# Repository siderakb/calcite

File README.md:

# Calcite

Kailh Choc V1 (aka PG1350) low profile switches ortho keyboard, includes PCB and CNC/3DP case, inspired by [ARTSEY](https://artsey.io/), [Home row mods](https://precondition.github.io/home-row-mods) and Preonic/Planck keyboard. 

> The keycap in the above picture is from Keychron K1 v2.

## Note

Gerber, BOM and CPL files are generated by [KiCad JLCPCB Tools](https://github.com/Bouni/kicad-jlcpcb-tools) plugin.  

I use [KiCAD KLE Placer](https://github.com/zykrah/kicad-kle-placer) plugin to automatically place switch footprints.

If `key-switches.pretty` folder is empty, use `git submodule update --init` to clone submodule.

## Disclaimer

These files are provided without warranty of any kind.  
It is recommended to check yourself before manufacturing and use.

For the full statement, plase see [LICENSE](./LICENSE).

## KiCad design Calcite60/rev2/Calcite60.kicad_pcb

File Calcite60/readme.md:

# Calcite60

A 60 keys ortho Kailh Choc V1 keyboard.

- Preonic V3 compatible (Mounting holes, USB and RESET button).
- Kailh Choc V1 low profile switches (PG1350), optional 2U keys.
- USB Type-C with ESD protection and resettable fuse.
- RP2040 ARM MCU, 16MB external flash.
- One configurable monochrome LED indicator.
- Powered by [QMK](https://github.com/qmk/qmk_firmware) firmware.
- Support [Vial](https://get.vial.today), edit keymap and configure keyboard in real time.
- JLCPCB's PCBA service available.

## PCB

Online preview available [here](https://kicanvas.org/?github=https%3A%2F%2Fgithub.com%2Fsiderakb%2Fcalcite%2Ftree%2Fmain%2FCalcite60%2Fpcb), powered by [KiCanvas](https://kicanvas.org/)

|        |               Preview                |
| ------ | :----------------------------------: |
| Front  |  |
| Back   |  |
| Layers |  |

### Board Characteristics

- Copper layer count: 2
- Board thickness: 1.6 mm
- Board overall dimensions: 226 mm x 94.15 mm
- Min track/spacing: 0.13 mm / 0.13 mm
- Min hole diameter: 0.3 mm
- Castellated pads: No
- Edge card connectors: No
- Plated board edge: No

## Screw

- 4* M2x2~4, 90° flat head

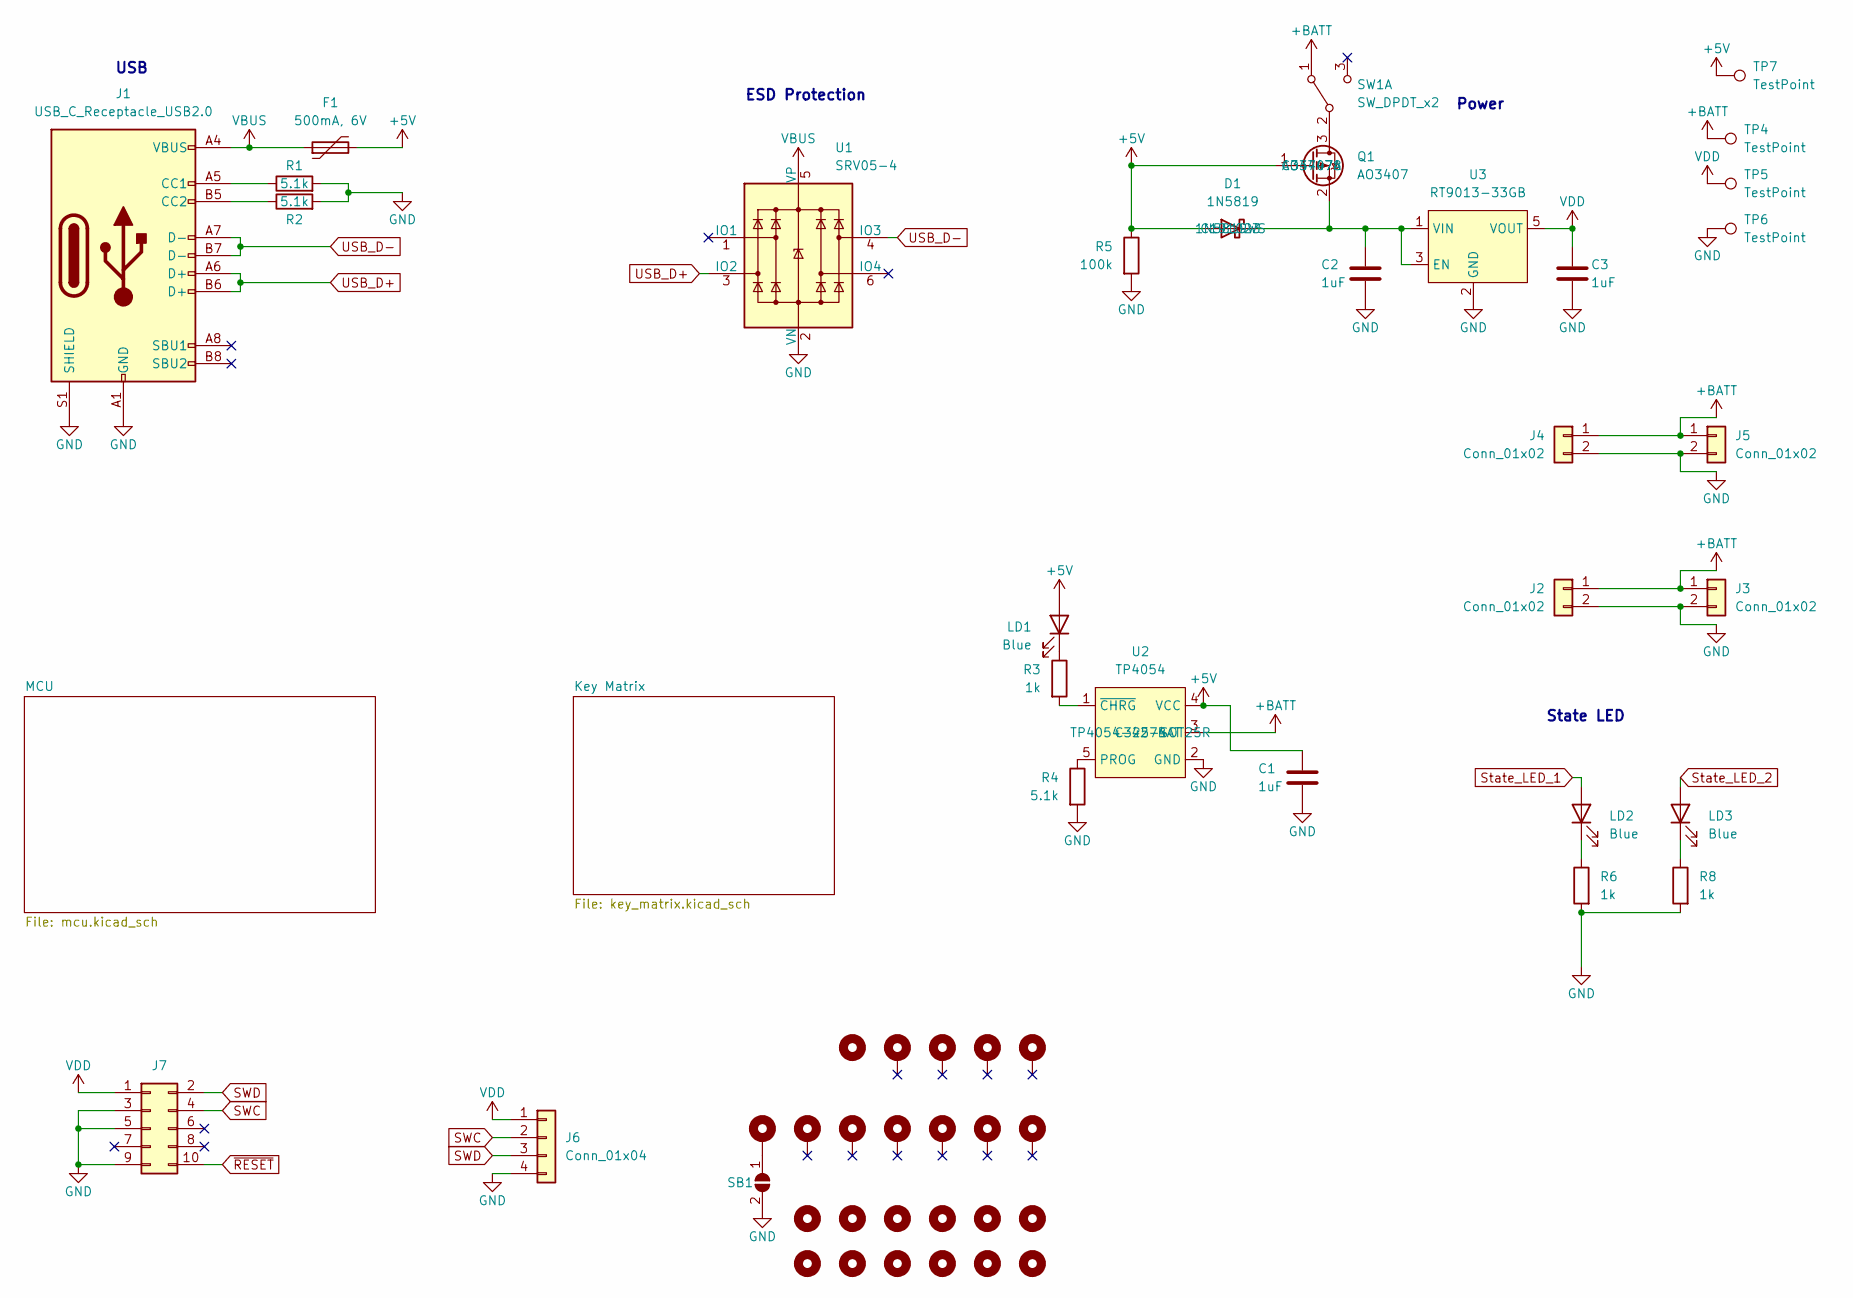
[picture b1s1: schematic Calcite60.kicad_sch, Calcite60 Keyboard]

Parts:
C1, C2, C3: 1uF; C_0603_1608Metric; MFR. Part # CL10A105KB8NNNC; LCSC C15849
D1: 1N5819; D_SOD-323_HandSoldering; MFR. Part # 1N5819WS; LCSC C191023
F1: 500mA, 6V; Fuse_0805_2012Metric; MFR. Part # SMD0805B050TF; LCSC C269104
H1, H2, H4, H6, H8, H10, H12, H14, H15, H16, H17: MountingHole; MountingWuerth_M2; MFR. Part # 9774025243R; LCSC C9900035855
H5, H18, H19, H20, H21, H22, H23, H24, H25: MountingHole; mouse_bite
H7, H9, H11, H13: MountingHole; MountingHale_M2
J1: USB_C_Receptacle_USB2.0; USB_C_Receptacle_HRO_TYPE-C-31-M-12; MFR. Part # TYPE-C-31-M-12; LCSC C165948
J2, J4: Conn_01x02; PinHeader_1x02_P2.54mm_Vertical
J3, J5: Conn_01x02; JST_PH_S2B-PH-K_1x02_P2.00mm_Horizontal
J6: Conn_01x04; PinHeader_1x04_P2.54mm_Vertical
J7: Conn_02x05_Counter_Clockwise; 10pin SWD
LD1, LD2, LD3: Blue; LED_0603_1608Metric; MFR. Part # 19-217/GHC-YR1S2/3T; LCSC C72043
Q1: AO3407; SOT-23; MFR. Part # AO3407A; LCSC C347478
R1, R2, R4: 5.1k; R_0603_1608Metric; MFR. Part # 0603WAF5101T5E; LCSC C23186
R3, R6, R8: 1k; R_0603_1608Metric; MFR. Part # 0603WAF1001T5E; LCSC C21190
R5: 100k; R_0603_1608Metric; MFR. Part # 0603WAF1003T5E; LCSC C25803
SB1: SolderJumper_2_Open; SolderJumper-2_P1.3mm_Open_TrianglePad1.0x1.5mm
SW1: SW_DPDT_x2; 9_3.5_3.5 Switch
TP4, TP5, TP6, TP7: TestPoint; TestPoint_Pad_D1.5mm
U1: SRV05-4; SOT-23-6; MFR. Part # SRV05-4-P-T7; LCSC C85364
U2: TP4054; SOT-23-5; MFR. Part # TP4054-42-SOT25R; LCSC C32574
U3: RT9013-33GB; SOT-23-5; MFR. Part # TPRT9013-33GB; LCSC C587158

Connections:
+5V: C1.1, D1.2 (A), F1.2, LD1.2 (A), Q1.1 (G), R5.1, TP7.1, U2.4 (VCC); also elsewhere on the board
+BATT: J2.1, J3.1, J4.1, J5.1, SW1.1 (A), TP4.1, U2.3 (BAT); also elsewhere on the board
GND: C1.2, C2.2, C3.2, J1.A1 (GND), J1.A12 (GND), J1.B1 (GND), J1.B12 (GND), J1.S1 (SHIELD), J2.2, J3.2, J4.2, J5.2, J6.4, J7.3, J7.5, J7.9, R1.2, R2.2, R4.2, R5.2, R6.2, R8.2, SB1.2 (B), TP6.1, U1.2 (VN), U2.2 (GND), U3.2 (GND); also elsewhere on the board
unnamed: C2.1, D1.1 (K), Q1.2 (S), U3.1 (VIN), U3.3 (EN)
unnamed: J1.A5 (CC1), R1.1
unnamed: J1.B5 (CC2), R2.1
unnamed: LD1.1 (K), R3.1
unnamed: LD2.1 (K), R6.1
unnamed: LD3.1 (K), R8.1
unnamed: Q1.3 (D), SW1.2 (B)
unnamed: H1.1, SB1.1 (A)
unnamed: R4.1, U2.5 (PROG)
unnamed: R3.2, U2.1 (~CHRG)
SWC: J6.2, J7.4; also elsewhere on the board
SWD: J6.3, J7.2; also elsewhere on the board
State_LED_1: LD2.2 (A); also elsewhere on the board
State_LED_2: LD3.2 (A); also elsewhere on the board
USB_D+: J1.A6 (D+), J1.B6 (D+), U1.3 (IO2); also elsewhere on the board
USB_D-: J1.A7 (D-), J1.B7 (D-), U1.4 (IO3); also elsewhere on the board
VBUS: F1.1, J1.A4 (VBUS), J1.A9 (VBUS), J1.B4 (VBUS), J1.B9 (VBUS), U1.5 (VP)
VDD: C3.1, J6.1, J7.1, TP5.1, U3.5 (VOUT); also elsewhere on the board
~RESET: J7.10; also elsewhere on the board

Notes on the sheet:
ESD Protection
State LED
USB
Power

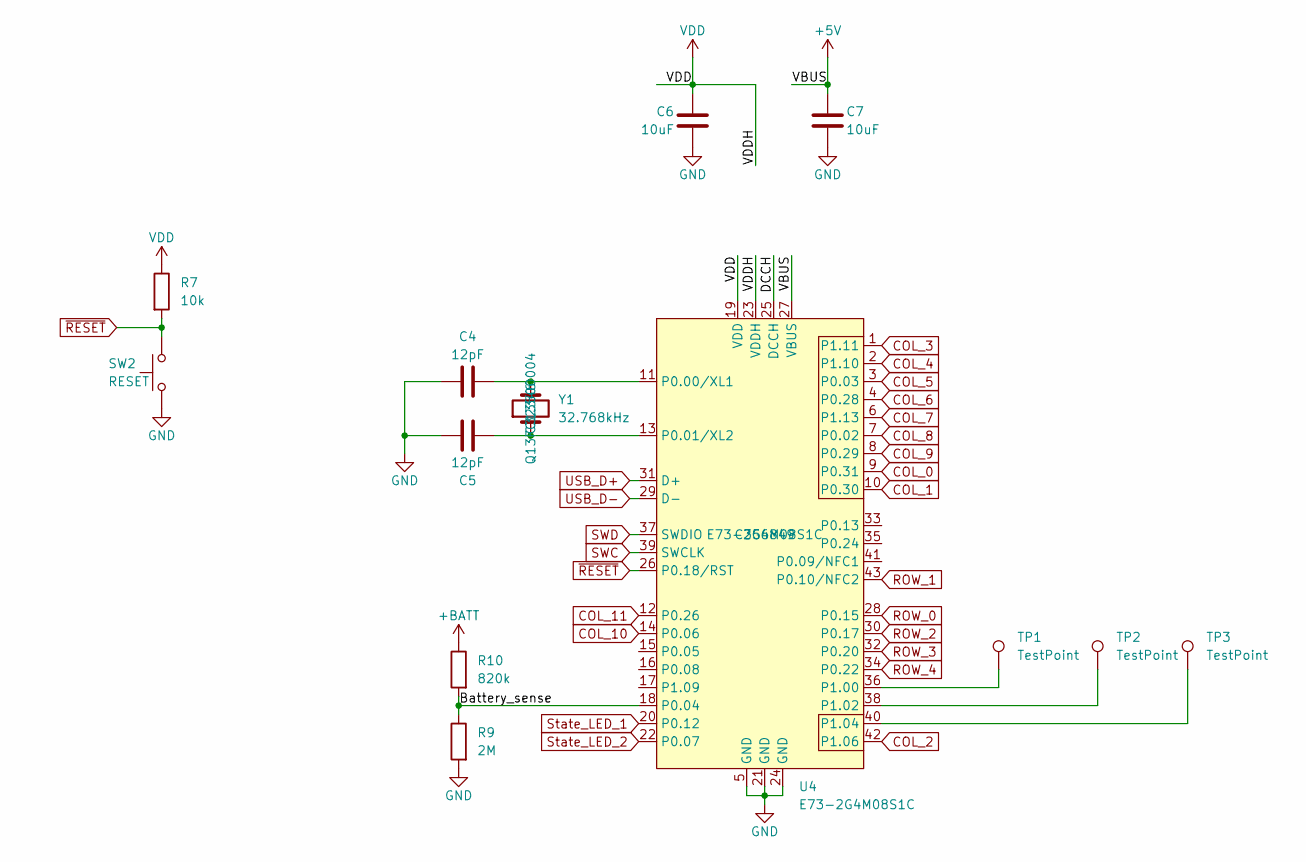
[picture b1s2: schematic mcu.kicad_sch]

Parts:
C4, C5: 12pF; C_0603_1608Metric; MFR. Part # CL10C120JB8NNNC; LCSC C38523
C6, C7: 10uF; C_0603_1608Metric; MFR. Part # CL10A106KP8NNNC; LCSC C19702
R7: 10k; R_0603_1608Metric; MFR. Part # 0603WAF1002T5E; LCSC C25804
R9: 2M; R_0603_1608Metric; MFR. Part # 0603WAF2004T5E; LCSC C22976
R10: 820k; R_0603_1608Metric; MFR. Part # 0603WAF8203T5E; LCSC C23252
SW2: RESET; SW_SPST_B3U-1000P; MFR. Part # TS-1064SA-A1B2-D4; LCSC C7464577
TP1, TP2, TP3: TestPoint; TestPoint_Pad_D1.5mm
U4: E73-2G4M08S1C; E73-2G4M08S1C-52840; MFR. Part # E73-2G4M08S1C; LCSC C356849
Y1: 32.768kHz; Crystal_SMD_3215-2Pin_3.2x1.5mm; MFR. Part # Q13FC13500004; LCSC C32346

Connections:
+5V: C7.1, U4.27 (VBUS); also elsewhere on the board
+BATT: R10.1; also elsewhere on the board
/MCU/Battery_sense: R9.1, R10.2, U4.18 (P0.04)
/MCU/DCCH: U4.25 (DCCH)
COL_0: U4.9 (P0.31); also elsewhere on the board
COL_1: U4.10 (P0.30); also elsewhere on the board
COL_2: U4.42 (P1.06); also elsewhere on the board
COL_3: U4.1 (P1.11); also elsewhere on the board
COL_4: U4.2 (P1.10); also elsewhere on the board
COL_5: U4.3 (P0.03); also elsewhere on the board
COL_6: U4.4 (P0.28); also elsewhere on the board
COL_7: U4.6 (P1.13); also elsewhere on the board
COL_8: U4.7 (P0.02); also elsewhere on the board
COL_9: U4.8 (P0.29); also elsewhere on the board
COL_10: U4.14 (P0.06); also elsewhere on the board
COL_11: U4.12 (P0.26); also elsewhere on the board
GND: C4.2, C5.1, C6.2, C7.2, R9.2, SW2.1, U4.5 (GND), U4.21 (GND), U4.24 (GND); also elsewhere on the board
unnamed: C4.1, U4.11 (P0.00/XL1), Y1.2
unnamed: C5.2, U4.13 (P0.01/XL2), Y1.1
unnamed: TP1.1, U4.36 (P1.00)
unnamed: TP2.1, U4.38 (P1.02)
unnamed: TP3.1, U4.40 (P1.04)
ROW_0: U4.28 (P0.15); also elsewhere on the board
ROW_1: U4.43 (P0.10/NFC2); also elsewhere on the board
ROW_2: U4.30 (P0.17); also elsewhere on the board
ROW_3: U4.32 (P0.20); also elsewhere on the board
ROW_4: U4.34 (P0.22); also elsewhere on the board
SWC: U4.39 (SWCLK); also elsewhere on the board
SWD: U4.37 (SWDIO); also elsewhere on the board
State_LED_1: U4.20 (P0.12); also elsewhere on the board
State_LED_2: U4.22 (P0.07); also elsewhere on the board
USB_D+: U4.31 (D+); also elsewhere on the board
USB_D-: U4.29 (D-); also elsewhere on the board
VDD: C6.1, R7.1, U4.19 (VDD), U4.23 (VDDH); also elsewhere on the board
~RESET: R7.2, SW2.2, U4.26 (P0.18/RST); also elsewhere on the board

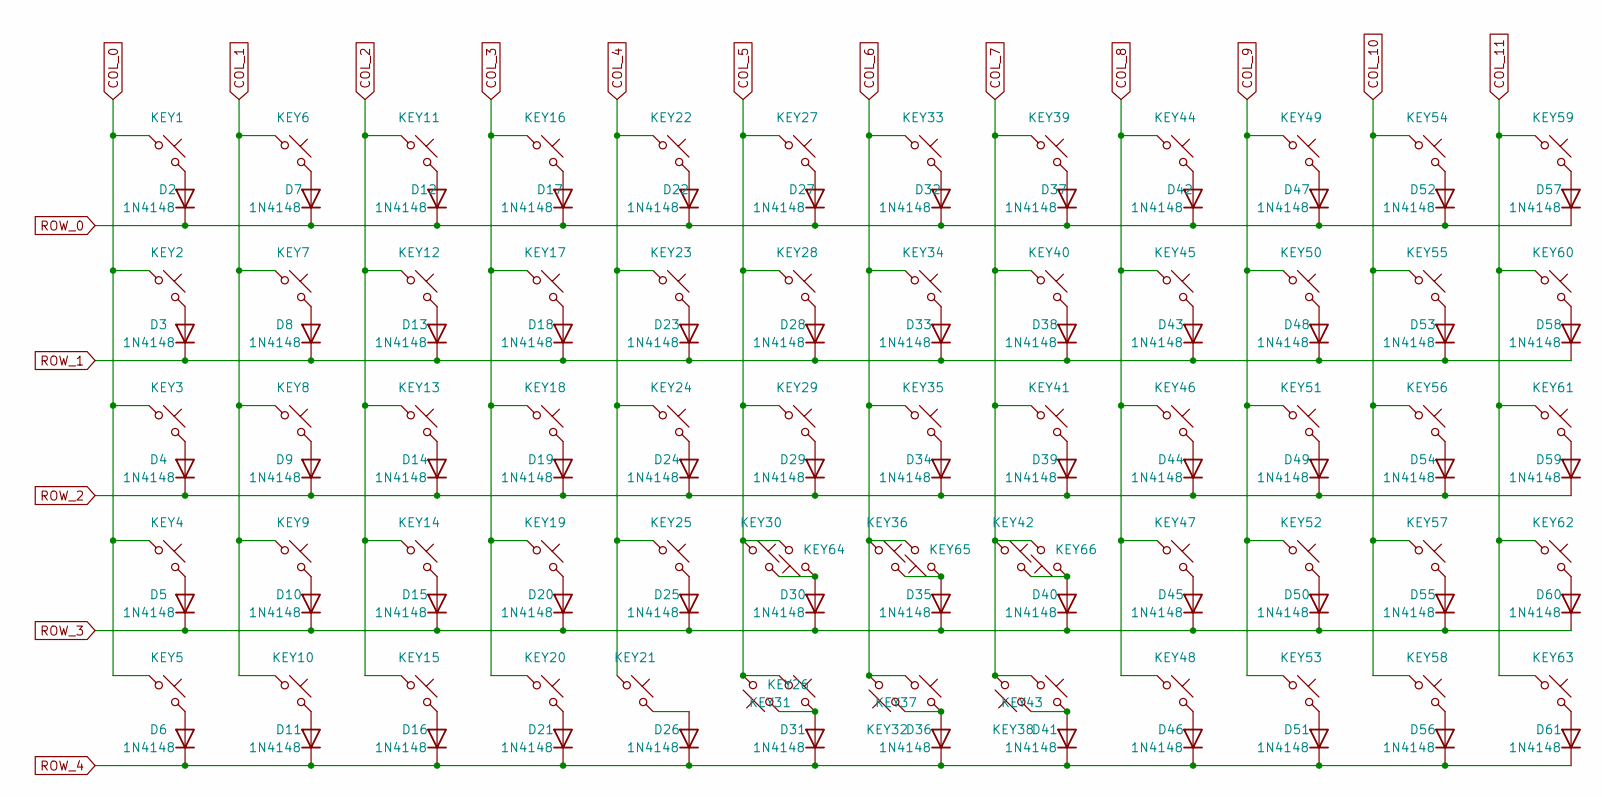
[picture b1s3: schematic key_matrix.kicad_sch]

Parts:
D2, D3, D4, D5, D6, D7, D8, D9, D10, D11, D12, D13, D14, D15, D16, D17, D18, D19, D20, D21, D22, D23, D24, D25, D26, D27, D28, D29, D30, D31, D32, D33, D34, D35, D36, D37, D38, D39, D40, D41, D42, D43, D44, D45, D46, D47, D48, D49, D50, D51, D52, D53, D54, D55, D56, D57, D58, D59, D60, D61: 1N4148; D_SOD-123; MFR. Part # 1N4148W; LCSC C81598
KEY1, KEY2, KEY3, KEY4, KEY5, KEY6, KEY7, KEY8, KEY9, KEY10, KEY11, KEY12, KEY13, KEY14, KEY15, KEY16, KEY17, KEY18, KEY19, KEY20, KEY21, KEY22, KEY23, KEY24, KEY25, KEY26, KEY27, KEY28, KEY29, KEY30, KEY31, KEY32, KEY33, KEY34, KEY35, KEY36, KEY37, KEY38, KEY39, KEY40, KEY41, KEY42, KEY43, KEY44, KEY45, KEY46, KEY47, KEY48, KEY49, KEY50, KEY51, KEY52, KEY53, KEY54, KEY55, KEY56, KEY57, KEY58, KEY59, KEY60, KEY61, KEY62, KEY63, KEY64, KEY65, KEY66: SW_Push_45deg; SW_Kailh_Choc_V1_THT_nSilk

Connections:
COL_0: KEY1.1, KEY2.1, KEY3.1, KEY4.1, KEY5.1; also elsewhere on the board
COL_1: KEY6.1, KEY7.1, KEY8.1, KEY9.1, KEY10.1; also elsewhere on the board
COL_2: KEY11.1, KEY12.1, KEY13.1, KEY14.1, KEY15.1; also elsewhere on the board
COL_3: KEY16.1, KEY17.1, KEY18.1, KEY19.1, KEY20.1; also elsewhere on the board
COL_4: KEY21.1, KEY22.1, KEY23.1, KEY24.1, KEY25.1; also elsewhere on the board
COL_5: KEY26.2, KEY27.1, KEY28.1, KEY29.1, KEY30.1, KEY31.1, KEY64.2; also elsewhere on the board
COL_6: KEY32.2, KEY33.1, KEY34.1, KEY35.1, KEY36.1, KEY37.1, KEY65.2; also elsewhere on the board
COL_7: KEY38.2, KEY39.1, KEY40.1, KEY41.1, KEY42.1, KEY43.1, KEY66.2; also elsewhere on the board
COL_8: KEY44.1, KEY45.1, KEY46.1, KEY47.1, KEY48.1; also elsewhere on the board
COL_9: KEY49.1, KEY50.1, KEY51.1, KEY52.1, KEY53.1; also elsewhere on the board
COL_10: KEY54.1, KEY55.1, KEY56.1, KEY57.1, KEY58.1; also elsewhere on the board
COL_11: KEY59.1, KEY60.1, KEY61.1, KEY62.1, KEY63.1; also elsewhere on the board
unnamed: D2.2 (A), KEY1.2
unnamed: D3.2 (A), KEY2.2
unnamed: D4.2 (A), KEY3.2
unnamed: D5.2 (A), KEY4.2
unnamed: D6.2 (A), KEY5.2
unnamed: D7.2 (A), KEY6.2
unnamed: D8.2 (A), KEY7.2
unnamed: D9.2 (A), KEY8.2
unnamed: D10.2 (A), KEY9.2
unnamed: D11.2 (A), KEY10.2
unnamed: D12.2 (A), KEY11.2
unnamed: D13.2 (A), KEY12.2
unnamed: D14.2 (A), KEY13.2
unnamed: D15.2 (A), KEY14.2
unnamed: D16.2 (A), KEY15.2
unnamed: D17.2 (A), KEY16.2
unnamed: D18.2 (A), KEY17.2
unnamed: D19.2 (A), KEY18.2
unnamed: D20.2 (A), KEY19.2
unnamed: D21.2 (A), KEY20.2
unnamed: D22.2 (A), KEY22.2
unnamed: D23.2 (A), KEY23.2
unnamed: D24.2 (A), KEY24.2
unnamed: D25.2 (A), KEY25.2
unnamed: D26.2 (A), KEY21.2
unnamed: D27.2 (A), KEY27.2
unnamed: D28.2 (A), KEY28.2
unnamed: D29.2 (A), KEY29.2
unnamed: D30.2 (A), KEY30.2, KEY64.1
unnamed: D31.2 (A), KEY26.1, KEY31.2
unnamed: D32.2 (A), KEY33.2
unnamed: D33.2 (A), KEY34.2
unnamed: D34.2 (A), KEY35.2
unnamed: D35.2 (A), KEY36.2, KEY65.1
unnamed: D36.2 (A), KEY32.1, KEY37.2
unnamed: D37.2 (A), KEY39.2
unnamed: D38.2 (A), KEY40.2
unnamed: D39.2 (A), KEY41.2
unnamed: D40.2 (A), KEY42.2, KEY66.1
unnamed: D41.2 (A), KEY38.1, KEY43.2
unnamed: D42.2 (A), KEY44.2
unnamed: D43.2 (A), KEY45.2
unnamed: D44.2 (A), KEY46.2
unnamed: D45.2 (A), KEY47.2
unnamed: D46.2 (A), KEY48.2
unnamed: D47.2 (A), KEY49.2
unnamed: D48.2 (A), KEY50.2
unnamed: D49.2 (A), KEY51.2
unnamed: D50.2 (A), KEY52.2
unnamed: D51.2 (A), KEY53.2
unnamed: D52.2 (A), KEY54.2
unnamed: D53.2 (A), KEY55.2
unnamed: D54.2 (A), KEY56.2
unnamed: D55.2 (A), KEY57.2
unnamed: D56.2 (A), KEY58.2
unnamed: D57.2 (A), KEY59.2
unnamed: D58.2 (A), KEY60.2
unnamed: D59.2 (A), KEY61.2
unnamed: D60.2 (A), KEY62.2
unnamed: D61.2 (A), KEY63.2
ROW_0: D2.1 (K), D7.1 (K), D12.1 (K), D17.1 (K), D22.1 (K), D27.1 (K), D32.1 (K), D37.1 (K), D42.1 (K), D47.1 (K), D52.1 (K), D57.1 (K); also elsewhere on the board
ROW_1: D3.1 (K), D8.1 (K), D13.1 (K), D18.1 (K), D23.1 (K), D28.1 (K), D33.1 (K), D38.1 (K), D43.1 (K), D48.1 (K), D53.1 (K), D58.1 (K); also elsewhere on the board
ROW_2: D4.1 (K), D9.1 (K), D14.1 (K), D19.1 (K), D24.1 (K), D29.1 (K), D34.1 (K), D39.1 (K), D44.1 (K), D49.1 (K), D54.1 (K), D59.1 (K); also elsewhere on the board
ROW_3: D5.1 (K), D10.1 (K), D15.1 (K), D20.1 (K), D25.1 (K), D30.1 (K), D35.1 (K), D40.1 (K), D45.1 (K), D50.1 (K), D55.1 (K), D60.1 (K); also elsewhere on the board
ROW_4: D6.1 (K), D11.1 (K), D16.1 (K), D21.1 (K), D26.1 (K), D31.1 (K), D36.1 (K), D41.1 (K), D46.1 (K), D51.1 (K), D56.1 (K), D61.1 (K); also elsewhere on the board

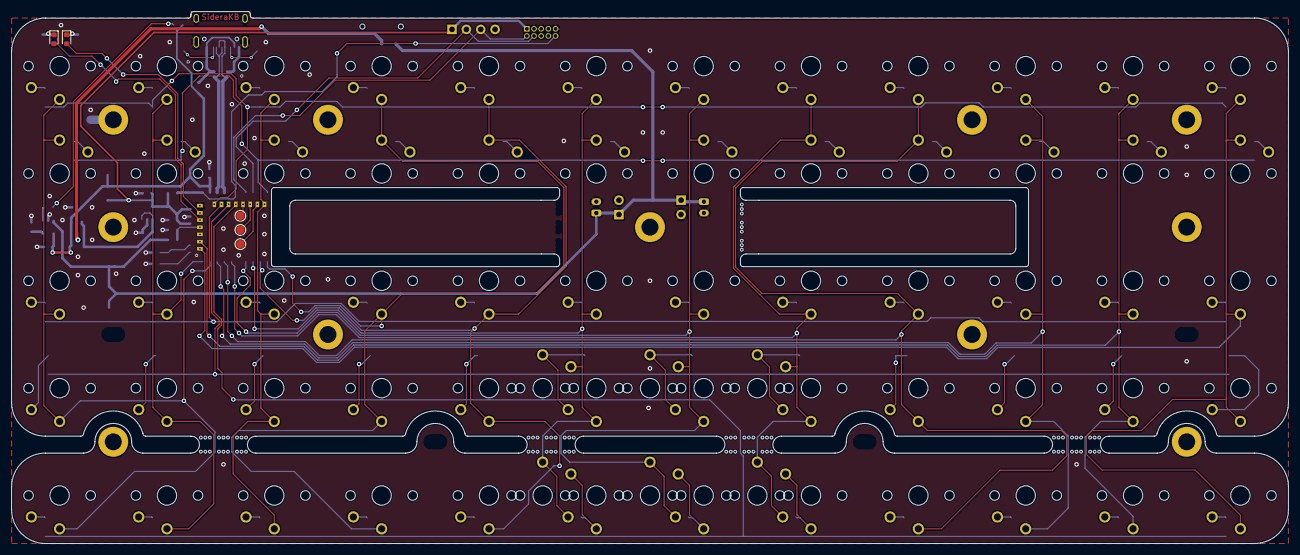
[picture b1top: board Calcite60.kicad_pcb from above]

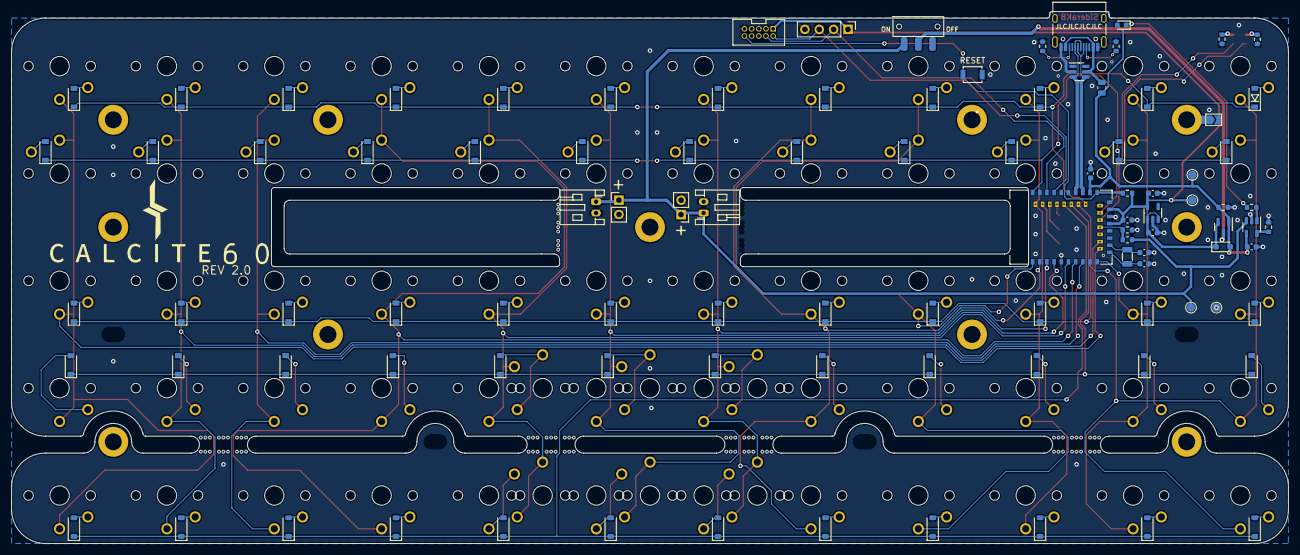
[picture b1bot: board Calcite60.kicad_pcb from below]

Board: 2 copper layers, 226.0 x 94.2 mm, 195 parts (111 on the bottom side), 105 nets.

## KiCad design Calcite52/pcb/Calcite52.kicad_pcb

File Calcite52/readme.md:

# Calcite52

- 52 keys ortho keyboard.
- Kailh Choc V1 low profile switches (PG1350).
- USB Type-C with ESD protection and resettable fuse.
- RP2040 ARM MCU, 16MB external flash.
- One configurable monochrome LED indicator.
- M2 screw mounting holes.
- USB D+/- pads for debugging.
- Powered by [QMK](https://github.com/qmk/qmk_firmware) firmware.
- Support [Vial](https://get.vial.today), edit keymap and configure keyboard in real time.
- JLCPCB's PCBA service available.

## PCB

PCB online preview avaliable [here](https://kicanvas.org/?github=https%3A%2F%2Fgithub.com%2Fsiderakb%2Fcalcite%2Ftree%2Fmain%2FCalcite52%2Fpcb), powered by KiCanvas.

|        |               Preview                |
| :----: | :----------------------------------: |
| Front  |  |
|  Back  |  |
| Layers |  |

### Board Characteristics

- Copper layer count: 2
- Board thickness: 1.6 mm
- Board overall dimensions: 231.14 mm x 97.79 mm
- Min track/spacing: 0.13 mm / 0.13 mm
- Min hole diameter: 0.3 mm
- Castellated pads: No
- Edge card connectors: No
- Plated board edge: No

## Case

- CNC: Designed using [onshape](https://cad.onshape.com/documents/40c7e2089f3d168efe6af68a/w/3670640f6bf03c896decab1c/e/fe064372e5ac08dff53a3881?renderMode=0&uiState=65b3d52ba4a899578972f582). I order aluminum 6061 + bead blast + anodized from PCBWay around 60 USD (June 2023).
- 3D Printing: Designed using FreeCAD. Please note that the 3D printed casing will bend easily and is not recommended.

## Firmware

Vial QMK firmware is available in [siderakb/vial-qmk repo](https://github.com/siderakb/vial-qmk/tree/siderakb/main/keyboards/siderakb/calcite52) (*siderakb/main* branch).

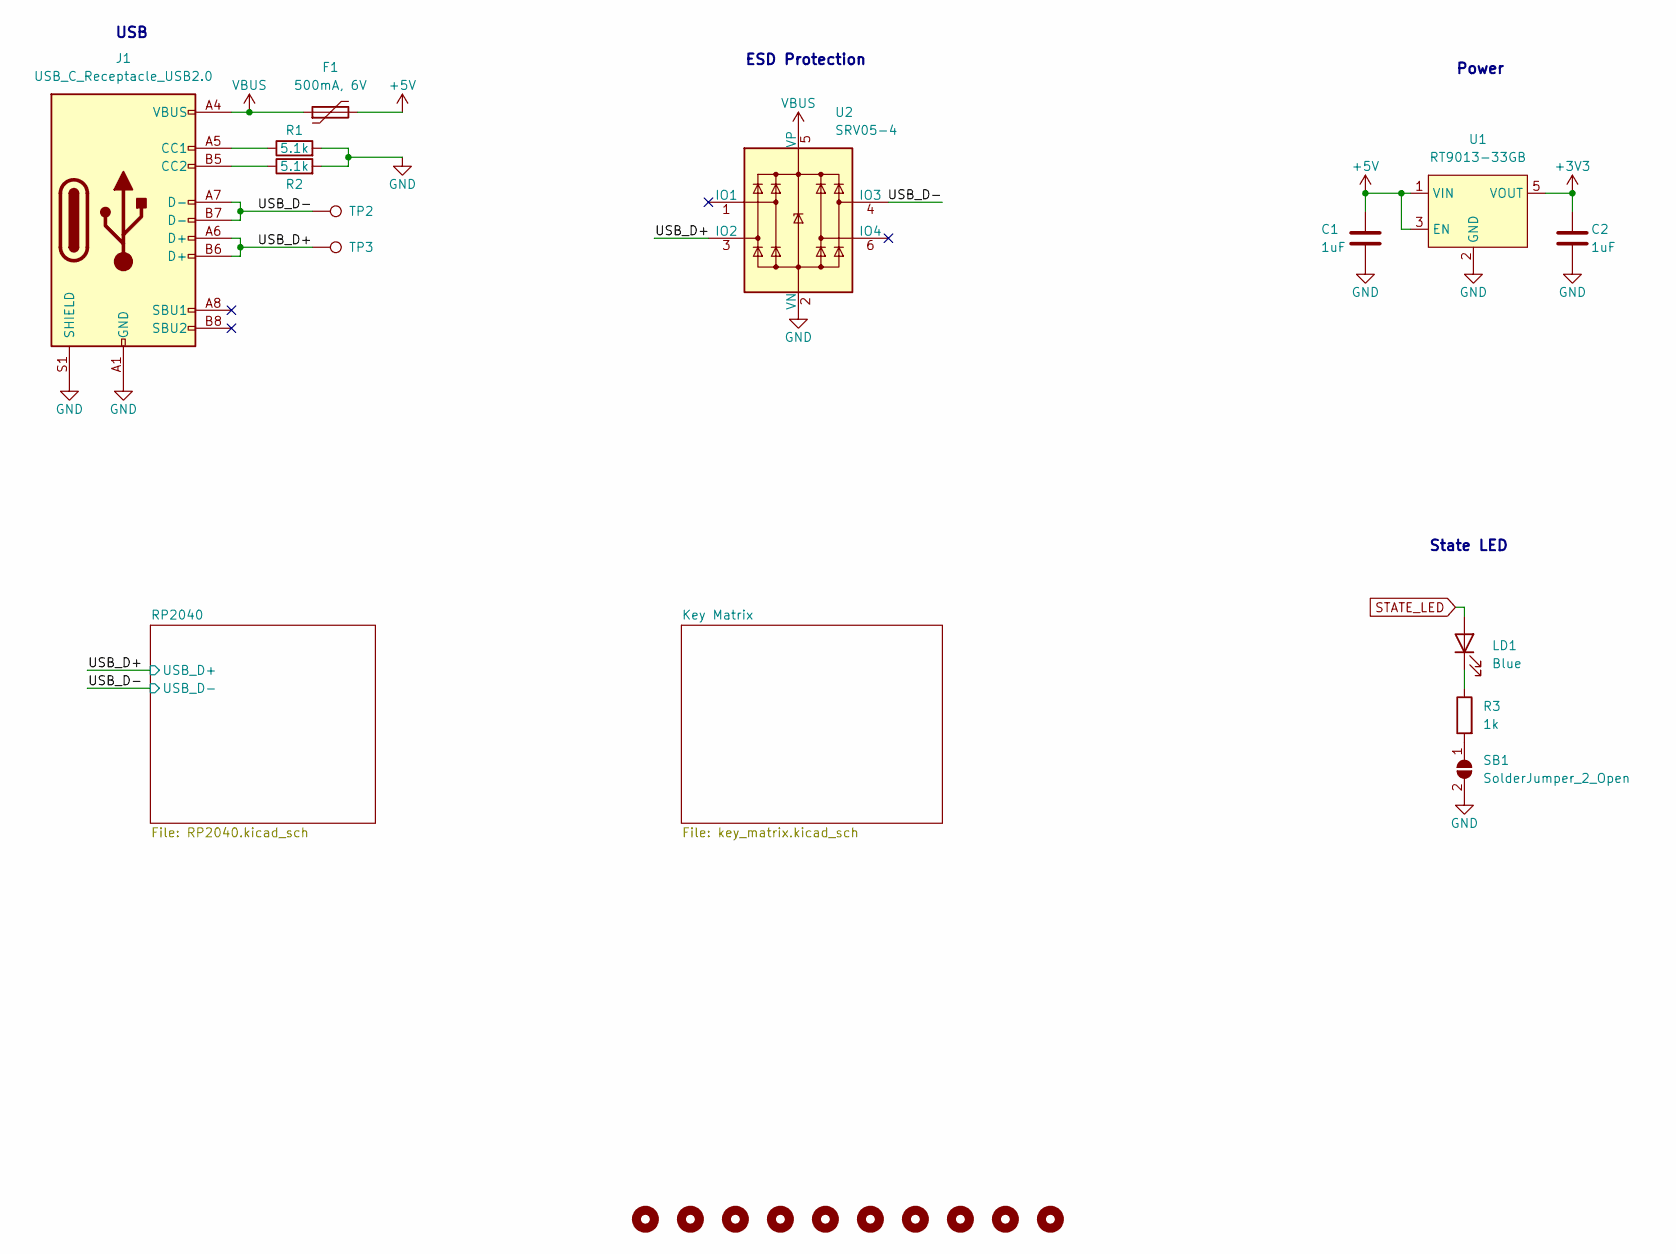
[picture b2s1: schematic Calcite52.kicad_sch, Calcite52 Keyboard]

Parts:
C1, C2: 1uF; C_0402_1005Metric; MFR. Part # CL05A105KA5NQNC; LCSC C52923
F1: 500mA, 6V; Fuse_0805_2012Metric; MFR. Part # SMD0805B050TF; LCSC C269104
H1, H2, H3, H4, H5, H6, H7, H8, H9, H10: MountingHole; MountingHole_2.2mm_M2
J1: USB_C_Receptacle_USB2.0; USB_C_Receptacle_HRO_TYPE-C-31-M-12; MFR. Part # TYPE-C-31-M-12; LCSC C165948
LD1: Blue; LED_0603_1608Metric; MFR. Part # 19-217/GHC-YR1S2/3T; LCSC C72043
R1, R2: 5.1k; R_0402_1005Metric; MFR. Part # 0402WGF5101TCE; LCSC C25905
R3: 1k; R_0402_1005Metric; MFR. Part # 0402WGF1001TCE; LCSC C11702
SB1: SolderJumper_2_Open; SolderJumper-2_P1.3mm_Open_TrianglePad1.0x1.5mm
TP2, TP3: TestPoint; TestPoint_Pad_1.5x1.5mm
U1: RT9013-33GB; SOT-23-5; MFR. Part # RT9013-33GB; LCSC C47773
U2: SRV05-4; SOT-23-6; MFR. Part # SRV05-4-P-T7; LCSC C85364

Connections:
+3V3: C2.1, U1.5 (VOUT); also elsewhere on the board
+5V: C1.1, F1.2, U1.1 (VIN), U1.3 (EN)
/USB_D+: J1.A6 (D+), J1.B6 (D+), TP3.1, U2.3 (IO2); also elsewhere on the board
/USB_D-: J1.A7 (D-), J1.B7 (D-), TP2.1, U2.4 (IO3); also elsewhere on the board
GND: C1.2, C2.2, J1.A1 (GND), J1.A12 (GND), J1.B1 (GND), J1.B12 (GND), J1.S1 (SHIELD), R1.2, R2.2, SB1.2 (B), U1.2 (GND), U2.2 (VN); also elsewhere on the board
unnamed: J1.A5 (CC1), R1.1
unnamed: J1.B5 (CC2), R2.1
unnamed: LD1.1 (K), R3.1
unnamed: R3.2, SB1.1 (A)
STATE_LED: LD1.2 (A); also elsewhere on the board
VBUS: F1.1, J1.A4 (VBUS), J1.A9 (VBUS), J1.B4 (VBUS), J1.B9 (VBUS), U2.5 (VP)

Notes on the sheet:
ESD Protection
State LED
USB
Power

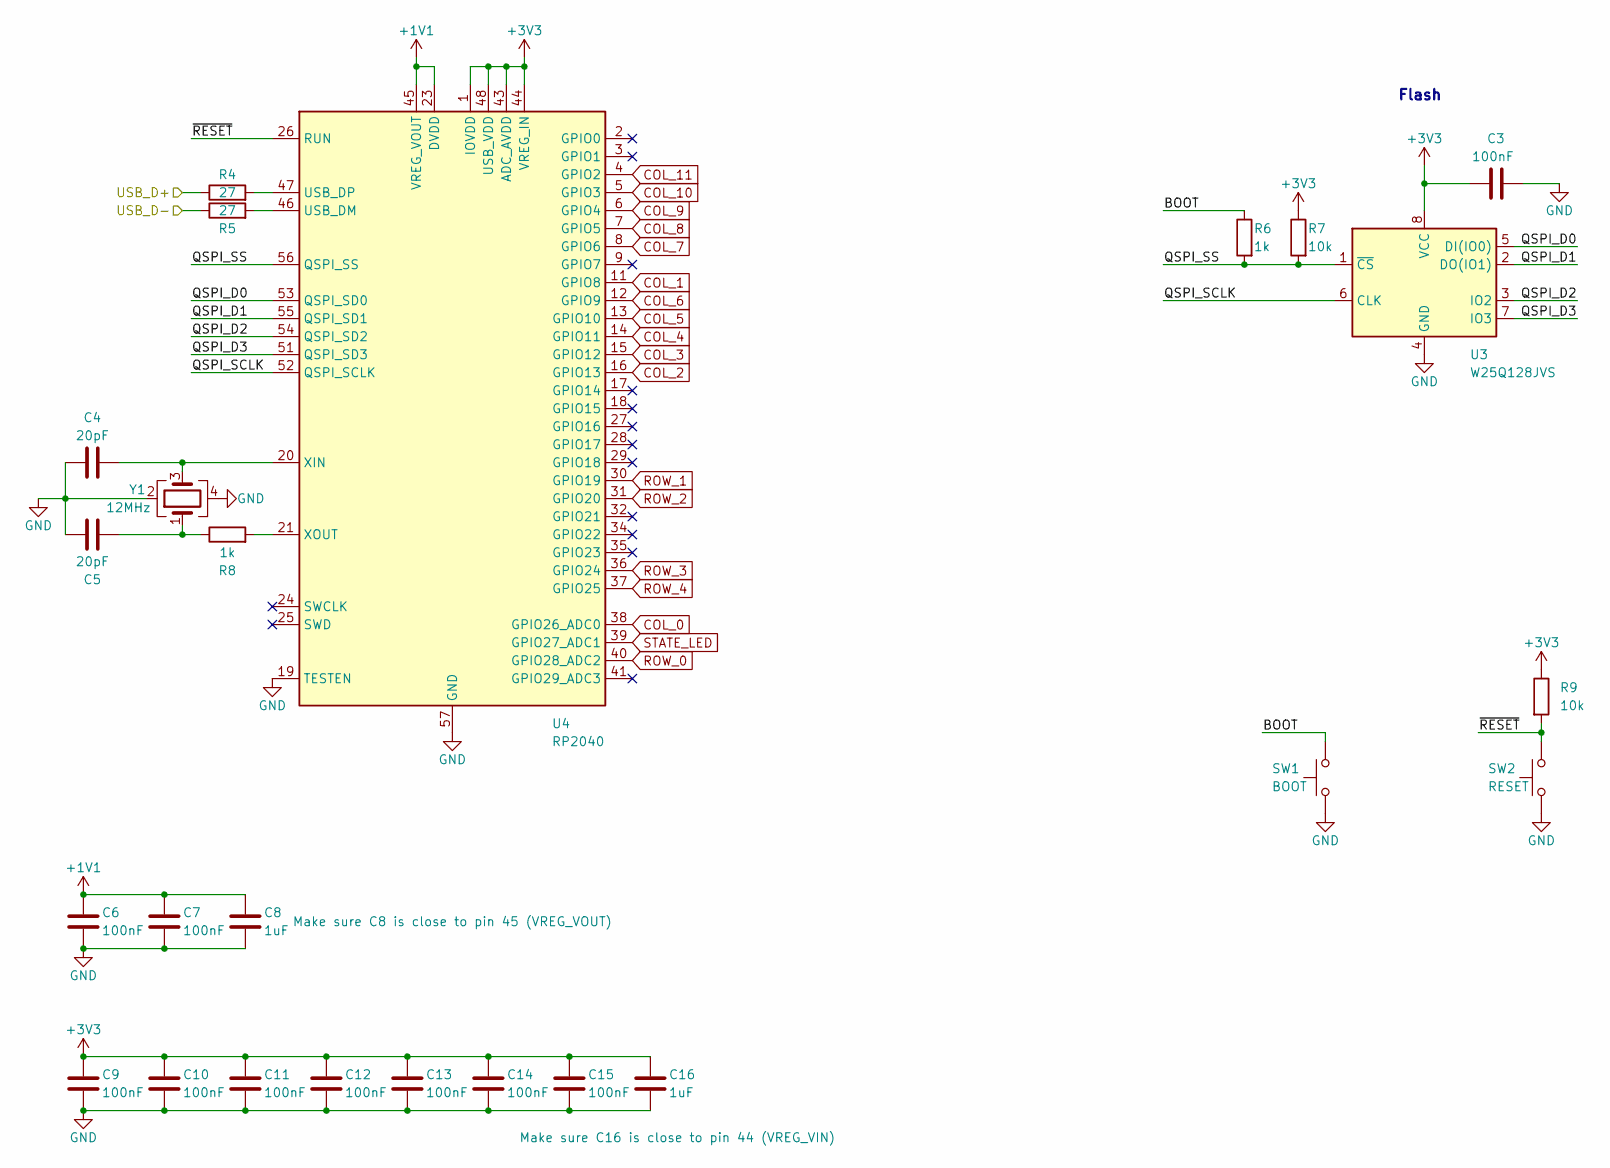
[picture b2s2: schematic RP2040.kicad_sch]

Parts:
C3, C6, C7, C9, C10, C11, C12, C13, C14, C15: 100nF; C_0402_1005Metric; MFR. Part # CL05B104KB54PNC; LCSC C307331
C4, C5: 20pF; C_0402_1005Metric; MFR. Part # 0402CG200J500NT; LCSC C1554
C8, C16: 1uF; C_0402_1005Metric; MFR. Part # CL05A105KA5NQNC; LCSC C52923
R4, R5: 27; R_0603_1608Metric; MFR. Part # 0603WAF270JT5E; LCSC C25190
R6, R8: 1k; R_0402_1005Metric; MFR. Part # 0402WGF1001TCE; LCSC C11702
R7, R9: 10k; R_0402_1005Metric; MFR. Part # 0402WGF1002TCE; LCSC C25744
SW1: BOOT; SW_SPST_CK_RS282G05A3; MFR. Part # GT-TC060B-H027-L1; LCSC C5117871
SW2: RESET; SW_SPST_CK_RS282G05A3; MFR. Part # GT-TC060B-H027-L1; LCSC C5117871
U3: W25Q128JVS; SOIC-8_5.23x5.23mm_P1.27mm; MFR. Part # W25Q128JVSIQ; LCSC C97521
U4: RP2040; QFN-56-1EP_7x7mm_P0.4mm_EP3.2x3.2mm; MFR. Part # RP2040; LCSC C2040
Y1: 12MHz; Crystal_SMD_3225-4Pin_3.2x2.5mm; MFR. Part # X322512MSB4SI; LCSC C9002

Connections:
+1V1: C6.1, C7.1, C8.1, U4.23 (DVDD), U4.45 (VREG_VOUT), U4.50 (DVDD)
+3V3: C3.1, C9.1, C10.1, C11.1, C12.1, C13.1, C14.1, C15.1, C16.1, R7.1, R9.1, U3.8 (VCC), U4.1 (IOVDD), U4.10 (IOVDD), U4.22 (IOVDD), U4.33 (IOVDD), U4.42 (IOVDD), U4.43 (ADC_AVDD), U4.44 (VREG_IN), U4.48 (USB_VDD), U4.49 (IOVDD); also elsewhere on the board
/RP2040/BOOT: R6.1, SW1.2
/RP2040/QSPI_D0: U3.5 (DI(IO0)), U4.53 (QSPI_SD0)
/RP2040/QSPI_D1: U3.2 (DO(IO1)), U4.55 (QSPI_SD1)
/RP2040/QSPI_D2: U3.3 (IO2), U4.54 (QSPI_SD2)
/RP2040/QSPI_D3: U3.7 (IO3), U4.51 (QSPI_SD3)
/RP2040/QSPI_SCLK: U3.6 (CLK), U4.52 (QSPI_SCLK)
/RP2040/QSPI_SS: R6.2, R7.2, U3.1 (~CS), U4.56 (QSPI_SS)
/RP2040/~RESET: R9.2, SW2.2, U4.26 (RUN)
/USB_D+: R4.1; also elsewhere on the board
/USB_D-: R5.1; also elsewhere on the board
COL_0: U4.38 (GPIO26_ADC0); also elsewhere on the board
COL_1: U4.11 (GPIO8); also elsewhere on the board
COL_2: U4.16 (GPIO13); also elsewhere on the board
COL_3: U4.15 (GPIO12); also elsewhere on the board
COL_4: U4.14 (GPIO11); also elsewhere on the board
COL_5: U4.13 (GPIO10); also elsewhere on the board
COL_6: U4.12 (GPIO9); also elsewhere on the board
COL_7: U4.8 (GPIO6); also elsewhere on the board
COL_8: U4.7 (GPIO5); also elsewhere on the board
COL_9: U4.6 (GPIO4); also elsewhere on the board
COL_10: U4.5 (GPIO3); also elsewhere on the board
COL_11: U4.4 (GPIO2); also elsewhere on the board
GND: C3.2, C4.1, C5.1, C6.2, C7.2, C8.2, C9.2, C10.2, C11.2, C12.2, C13.2, C14.2, C15.2, C16.2, SW1.1, SW2.1, U3.4 (GND), U4.19 (TESTEN), U4.57 (GND), Y1.2, Y1.4; also elsewhere on the board
unnamed: C4.2, U4.20 (XIN), Y1.3
unnamed: C5.2, R8.1, Y1.1
unnamed: R4.2, U4.47 (USB_DP)
unnamed: R5.2, U4.46 (USB_DM)
unnamed: R8.2, U4.21 (XOUT)
ROW_0: U4.40 (GPIO28_ADC2); also elsewhere on the board
ROW_1: U4.30 (GPIO19); also elsewhere on the board
ROW_2: U4.31 (GPIO20); also elsewhere on the board
ROW_3: U4.36 (GPIO24); also elsewhere on the board
ROW_4: U4.37 (GPIO25); also elsewhere on the board
STATE_LED: U4.39 (GPIO27_ADC1); also elsewhere on the board

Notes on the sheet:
Flash

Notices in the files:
Calcite52/Calcite52.kicad_sch:
MIT License (Open source hardware)
Calcite52/pcb/Calcite52.kicad_pcb:
Open source hardware, CERN-OHL-P v2
